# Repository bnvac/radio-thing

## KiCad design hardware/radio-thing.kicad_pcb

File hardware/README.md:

# Radio Thing — main board, rev A (KiCad 9)

One PCB for both builds:

- **POD:** 82 × 50 mm. Cut the button tab off at its 5 small bridges (flush cutters or a saw, then sand).
- **DISPLAY:** 82 × 72 mm. Keeps the tab with 3 buttons (UP · OK · DOWN) centred right under the screen.

## Status

| Step | State |
|---|---|
| Schematic | ✅ Generated, KiCad ERC: 1 warning (unused IMU aux pin tied to GND, expected) |
| Netlist | ✅ 304 pin assignments verified against `design.py`, 30 MCU pins verified against `firmware/include/board_pins.h` |
| PCB placement | ✅ Power stages and sensors placed tight around their IC pins; every pad on its net. |
| PCB routing | ✅ **Fully routed** (multi-pass Freerouting + fixed USB-C and U3 ground patterns): 932 track segments, 107 vias. DRC: **0 unconnected, 0 electrical errors, 0 schematic-parity issues**. 6 silkscreen-at-edge warnings remain, all expected (USB-C and the power switch overhang the edge by design). |
| Manufacturing files | ✅ `fab/`: Gerbers + drill (zip), and BOM + placement (CPL) for each build |
| Datasheet checks | ✅ Done 2026-10-20. 13 fixes applied; 5 items need the real parts in hand (see below). |

**Electrically complete and orderable as a prototype.** Before ordering: check the 5 open items below with real parts in hand, and look over the routing in KiCad (see "Review before ordering").

## Files

| File | What |
|---|---|
| `design.py` | **Source of truth.** Every part, value, footprint, and pin→net connection, plus the build variant. Edit this, not the KiCad files. |
| `tools/gen_schematic.py` | Generates `radio-thing.kicad_sch` + `radio-thing.kicad_sym` (custom MAX17048 symbol). Pins come from KiCad's own symbol library, so pin numbers aren't hand-typed. |
| `tools/check_netlist.py` | Checks KiCad's exported netlist against `design.py` and the firmware pin map |
| `tools/gen_pcb.py` | Generates the placed board: outline with break-off slots, 4 layers (In1 = solid GND), cluster placement around each IC, edge keep-outs, the fixed USB-C pattern, nets from the netlist |
| `route.sh` | Autoroutes the placed board (Freerouting 1.9.0, up to three passes), adds GND pours on top/bottom, fills, runs DRC |
| `tools/finish_pcb.py`, `tools/silk_cleanup.py` | Route import, pours, fill, silkscreen tidy-up, place/drill origin |
| `tools/fab_outputs.py` | Writes `fab/`: Gerber+drill zip, `bom-POD.csv`, `bom-DISPLAY.csv`, `cpl-POD.csv`, `cpl-DISPLAY.csv` (JLCPCB column format) |
| `build.sh` | Regenerates schematic + placed board, runs ERC, netlist check, DRC, BOM, PDF |
| `radio-thing.kicad_pcb` | **The routed board** (output of `route.sh`) |
| `bom.csv` | BOM grouped by value/footprint/**Variant** (BOTH / POD / DISP) |
| `radio-thing-schematic.pdf` | Printable schematic |
| `reports/` | Latest ERC/DRC reports and router logs |

Full rebuild:
```sh
export KICAD_SYMBOL_DIR=…/kicad-symbols KICAD_FOOTPRINT_DIR=…/kicad-footprints   # KiCad 9 libraries
./build.sh                                             # schematic + placed board + checks
FREEROUTING_JAR=…/freerouting-1.9.0.jar ./route.sh     # needs Java 17+ and xvfb-run
python3 tools/fab_outputs.py                           # Gerbers, drill, BOM, CPL
```

> If you hand-edit the routing in KiCad, **stop running build.sh/route.sh**, because they regenerate the board from scratch. From then on, edit in KiCad and use *Tools → Update PCB from Schematic*. `design.py` is then documentation only.

## Block diagram

```
USB-C ─ F1 ─ U1 ESD ─┬─ VBUS ─ U2 BQ24074 (power path, ~1 A in, 445 mA charge)
                     │            ├─ VBAT ─ J2 LiPo 1S ── U3 MAX17048 fuel gauge (I2C)
                     │            └─ VSYS ─┬─ SW1 power ─ U4 TPS63001 ─ +3V3 (ESP32, sensors, display)
                     │                     ├─ U5 TPS61202 ─ FB1/C13 LC filter ─ +5V_HEAD ─ J4 radar head [POD]
                     │                     └─ BZ1 buzzer [DISP]
                     └─ USB D+/D- ─ U6 ESP32-S3-WROOM-1U (U.FL → SMA)
U6 ── I2C ── U7 ISM330DHCX (IMU) + U8 LIS2MDL (compass) + U3
U6 ── SPI ── J3 ST7796 3.5" display [DISP]
U6 ── UART1/UART2 + HEAD_ID + HEAD_EN ── J4 JST-GH 10p radar head [POD]
U6 ── 3 buttons UP/OK/DOWN [DISP] (OK on both builds), RGB LED, buzzer
```

## Build variants

| Variant | Fitted on | Parts |
|---|---|---|
| BOTH | every board | USB-C, charger, fuel gauge, 3V3, ESP32, sensors, LED, OK button |
| POD | pod | 5 V boost + filter, radar head connector J4, head ID |
| DISP | display | display socket + backlight resistor, UP and DOWN buttons, buzzer. Change **R7 to 1k** for ~890 mA charging of a 2000 mAh cell. |

## Pin map (ESP32-S3-WROOM-1U-N8R8)

Defined in `firmware/include/board_pins.h`, the single source of truth, and checked automatically.

| GPIO | Net | GPIO | Net |
|---|---|---|---|
| 0 | BOOT | 15 | spare (TP2) |
| 1 | HEAD_ID (ADC) | 16 | BUZZER |
| 2 | HEADB_RX | 17 | CHG_N |
| 4 | BTN_UP | 18 | I2C_SCL |
| 5 | BTN_DOWN | 19/20 | USB D-/D+ |
| 6 | BTN_OK (wake) | 21 | LCD_BL |
| 7 | spare (TP1) | 38/47/48 | LED R/G/B |
| 8 | I2C_SDA | 39/40 | HEADA TX/RX |
| 9 | LCD_DC | 41 | HEAD_EN |
| 10 | SPI_CS | 42 | HEADB_TX |
| 11/12/13 | MOSI/SCK/MISO | 43/44 | debug UART |
| 14 | LCD_RST | 3, 45, 46, 35–37 | unused (strapping / PSRAM) |

GPIO7 and GPIO15 are spare (test pads TP1/TP2), e.g. for an IMU interrupt or touch later.

**Buttons (3, under the screen):** UP short = up/zoom in, hold = cycle mode · OK short = select/menu, hold 1.5 s = back (map: next pod), hold 3 s = sleep · DOWN short = down/zoom out. The buttons are centred on board x = 48.8 mm, which is the centre line of the enclosure. The 98 mm screen is centred in the case and connects to J3 with a short 14-wire ribbon (see `../enclosure/README.md`).

## Datasheet check (2026-10-20)

Every value that came from memory was checked against the manufacturer datasheets: TI BQ2407x SLUS810N, TPS6300x SLVS520C, TPS6120x SLVS577E, Maxim MAX17048 19-6171 r7, ST ISM330DHCX r4, LIS2MDL r5, Qorvo DWM3000 rev B, Espressif WROOM-1/1U v1.8, Hi-Link LD2450 protocol v1.03, and lcdwiki MSP3525/3526.

**Fixed after the check**

| Part | Was | Now | Why |
|---|---|---|---|
| R6 BQ24074 ITERM | 15k | **3.0k** | 15k ends the charge at 50% of ICHG (the max allowed). 3.0k gives the normal 10%. |
| R4 BQ24074 ILIM | 1.5k (~1.07 A) | **1.78k (~0.9 A)** | Stay within a default USB-C source's 900 mA |
| L1 TPS63001 | 1.5 µH | **2.2 µH** | The value TI characterises. Loop compensation assumes it. |
| TPS63001 VINA | direct | **100 Ω + 100 nF RC** | TI reference circuit |
| C11 TPS61202 VOUT | 10 µF | **22 µF** | Datasheet minimum ≈ 5 × L = 11 µF, before DC-bias derating |
| C20 LIS2MDL C1 | 100 nF | **220 nF** | Required value (Table 2). Plus **10 µF** on Vdd (C25). |
| C5 MAX17048 VDD | 1 µF | 100 nF | Datasheet value |
| Display power | +3V3 | **switched VSYS (PWR_EN)** | The module has its own 3.3 V LDO, and powering it from 3V3 would starve the backlight. Using the switched rail keeps it fully off when SW1 is off. |
| Backlight drive | P-FET high-side switch | **GPIO → 100 Ω → LED pin** | On the MSP3525 the LED pin is a logic input with a pull-up, so the old switch could never turn the backlight off |
| J3 pin 14 | NC | **SD_CS pulled high** | The module's SD card shares MISO |
| Buzzer | from VSYS (4.4 V, ~8.5 Ω coil) | **+3V3 via 15 Ω, flyback on coil** | The transducer is rated 2–4 V and ≤150 mA mean |
| Radar head UART | direct | **100 Ω series ×4** | Detachable connector: limits back-powering and ESD |
| Button tab | no holes | **2 × M3 holes** | Button presses would otherwise bend the board at the break line |
| Tab break line | V-score | **routed slots + 5 solid bridges** | A V-cut severs every copper layer, which would cut the button traces on the DISPLAY build too |
| DWM3000 option | footprint on board | **removed from rev A** | Its antenna keep-out blocked routing; pod-to-pod ranging moves to rev B |

**Confirmed correct:**
- BQ24074 pinout, EN1/EN2 mode, ISET (445 mA / 890 mA), TMR 46.4k (6.2 h), TS 10k, /CE, caps.
- TPS63001 pinout, PS/SYNC, FB, current margin.
- TPS61202 pinout, PS, UVLO-to-VIN, load disconnect, 2.2 µH, 600 mA at 5 V.
- MAX17048 pinout, wiring and registers.
- ISM330DHCX pinout, unused-pin handling and registers.
- LIS2MDL pinout, CS and address.
- ESP32-S3 strapping, EN RC, PSRAM pins, module pin numbers.
- LD2450 needs 5 V / >200 mA with a 3.3 V UART at 256000 baud.

**Still open (check with the real parts):**
1. **Display:** buy the **lcdwiki MSP3525 (ST7796)** module; the board is wired for its pinout. MSP3520/3521 is an ILI9488 board with different touch pins. The module is 98 × 55.5 mm with the header centred on its short edge, so check J3 and the button positions against the module before ordering.
2. **Buzzer:** KCG0601 has no datasheet online. Buy any 3 V, ~3 kHz, 6.5 mm external-drive magnetic transducer and confirm its footprint.
3. **MAX17048:** exposed-pad size (0.8 × 1.2 mm in the footprint) vs Maxim land pattern 90-0065. Also check stock/lifecycle.
4. **USBLC6-2SC6:** pinout confirmed from secondary sources only.
5. **LD2450 head board:** connector pin order and pitch (only shown as an image in Hi-Link's manual).

## Routing notes

- **Stackup:** F.Cu parts/signals · In1 solid GND · In2 power + signals · B.Cu signals. GND pours on F.Cu and B.Cu. Power ICs' thermal pads have solid (not spoked) GND connections.
- **Traces:** signals 0.2 mm / 0.127 mm clearance; power nets 0.3 mm (about 1.3 A on outer 1 oz copper at a 20 °C rise, above the ~1.2 A worst case on VSYS). Vias 0.6/0.3 mm (power 0.8/0.4).
- **Power stages:** each converter's inductor and input/output capacitors sit directly at the IC pins (placed by `gen_pcb.py` around U2/U4/U5), so the switching loops are short.
- **USB:** D+/D- are full-speed (12 Mbit/s), so no controlled impedance is needed. The two orientation pin pairs on the USB-C connector are joined with a fixed pattern (D- loop on top, D+ jumper on the bottom via two vias).
- **Edges:** tracks and vias stay at least 0.35 mm from every edge and slot.
- **Break-off tab:** 4 routed slots (1.5 mm wide) with 5 bridges (three 6–7 mm bridges in the middle carry the button traces). The button traces cross through the bridges, so the DISPLAY build keeps them intact. For the POD build, cut the bridges.

## Review before ordering

The routing came from an autorouter, so give it a look in KiCad before you pay for boards:
1. Open `radio-thing.kicad_pcb` and run DRC (it should show only the 6 expected silkscreen-edge warnings).
2. Look at the power stages (U2, U4, U5): short, direct connections from the inductors and caps to the IC pins.
3. Check the 5 open part items above. The display module position matters most.
4. **Fab:** JLCPCB 4-layer, 1.6 mm, 1 oz, ENIG. Upload `fab/radio-thing-revA-gerbers.zip`. For assembly, upload the BOM + CPL for the build you want (`bom-POD.csv` + `cpl-POD.csv`, or the DISPLAY pair). Fill in the LCSC part numbers, and check part rotations in their preview. The 12 mm buttons, display socket and debug header are through-hole: hand-solder them or select THT assembly.
5. **Mechanical:** M3 holes at the corners and on the tab, an SMA bulkhead pigtail from the U6 U.FL, and display standoffs.

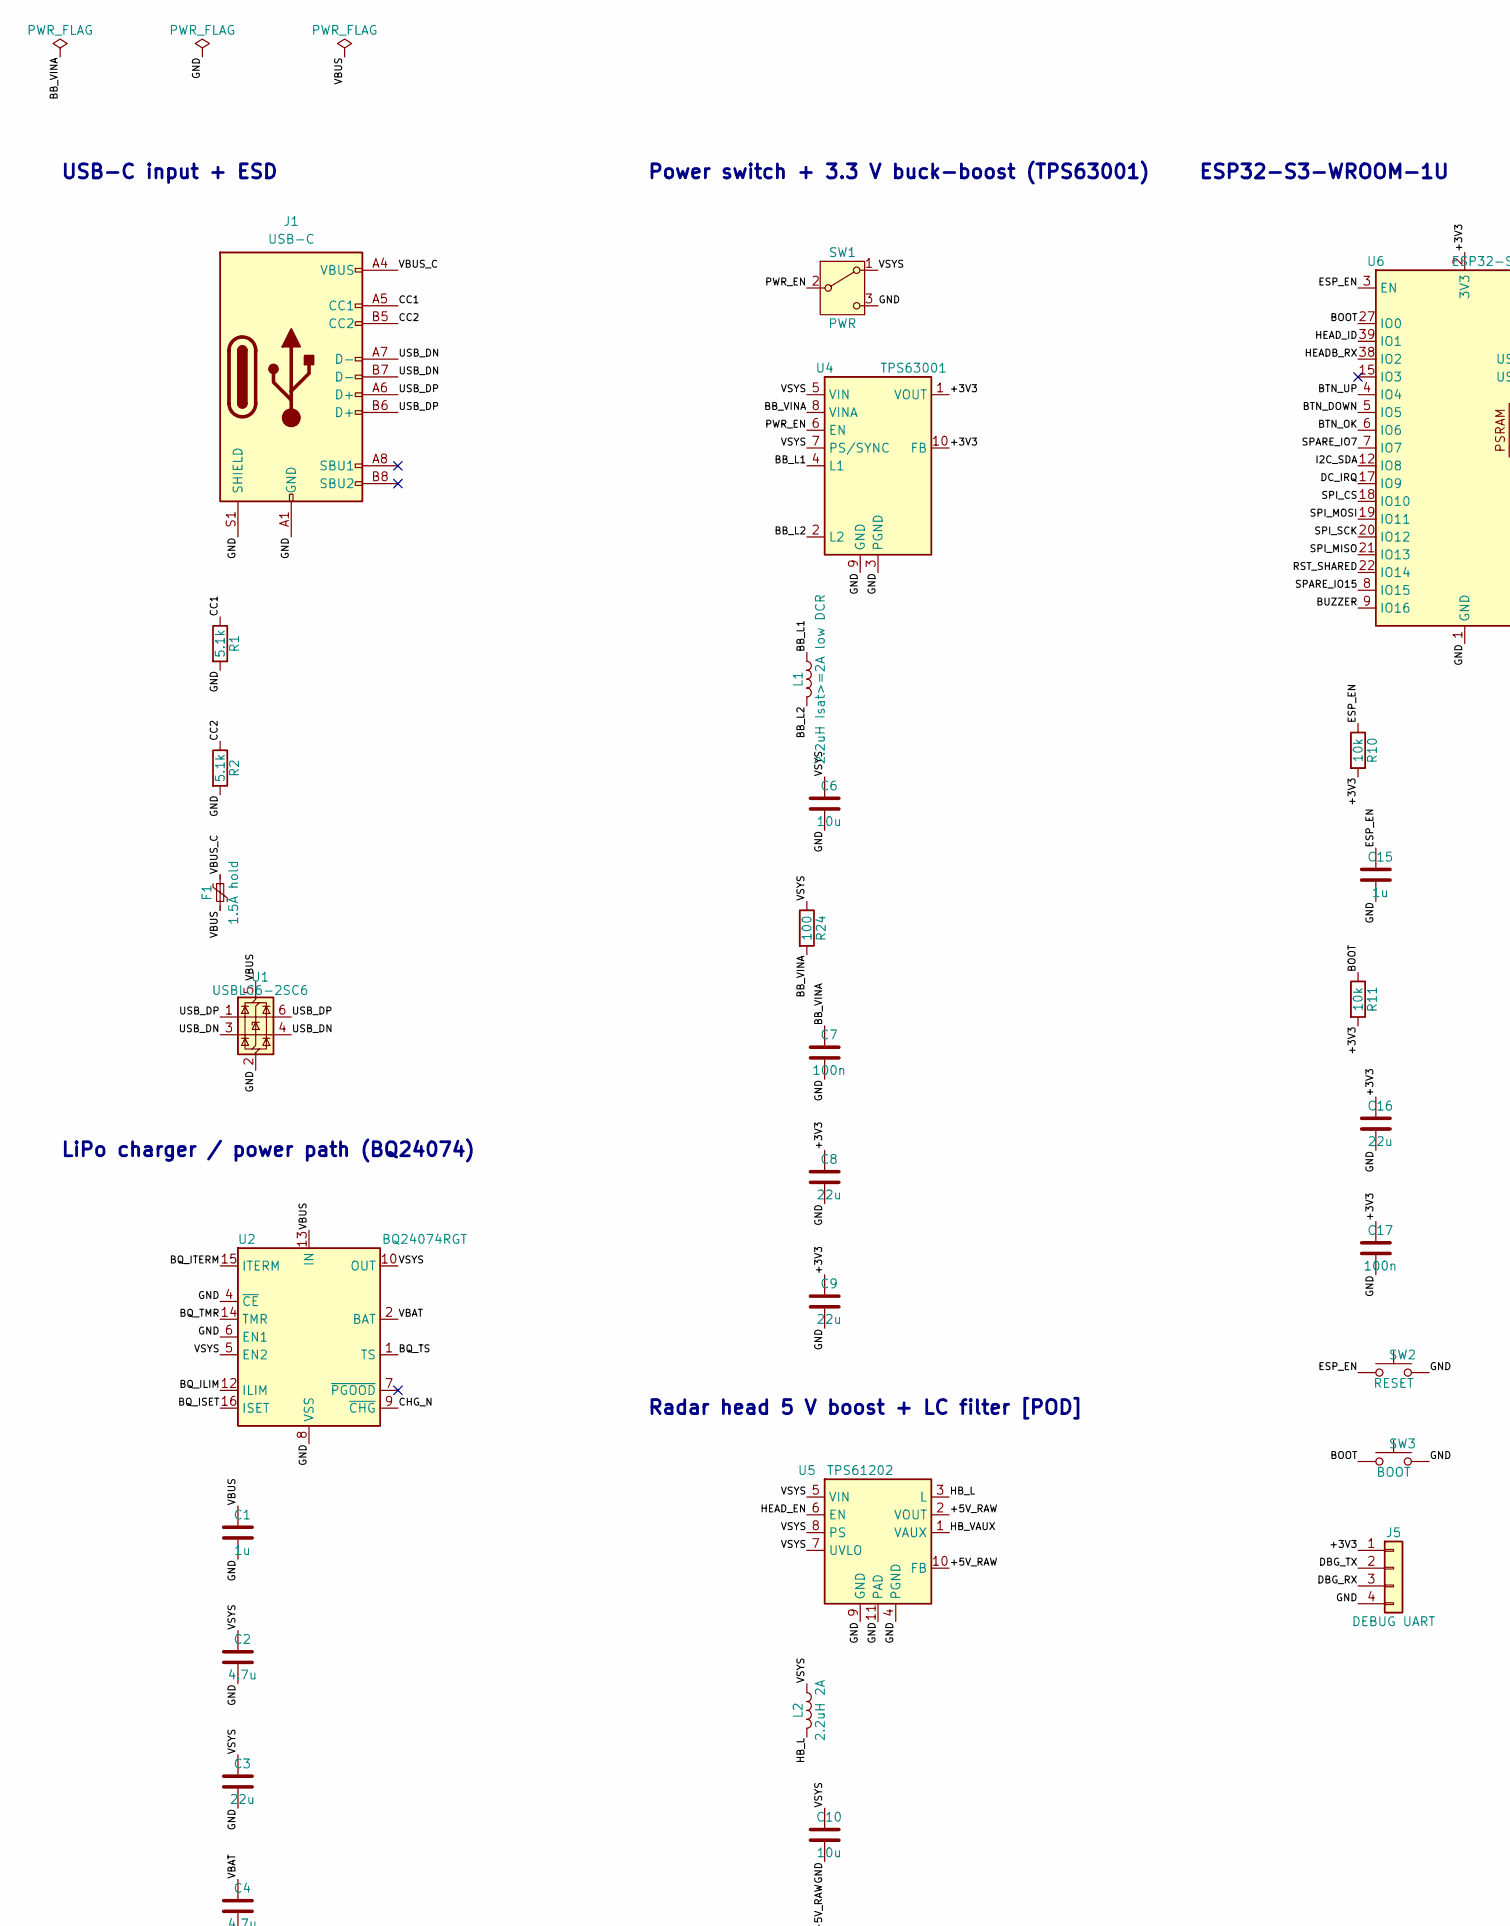
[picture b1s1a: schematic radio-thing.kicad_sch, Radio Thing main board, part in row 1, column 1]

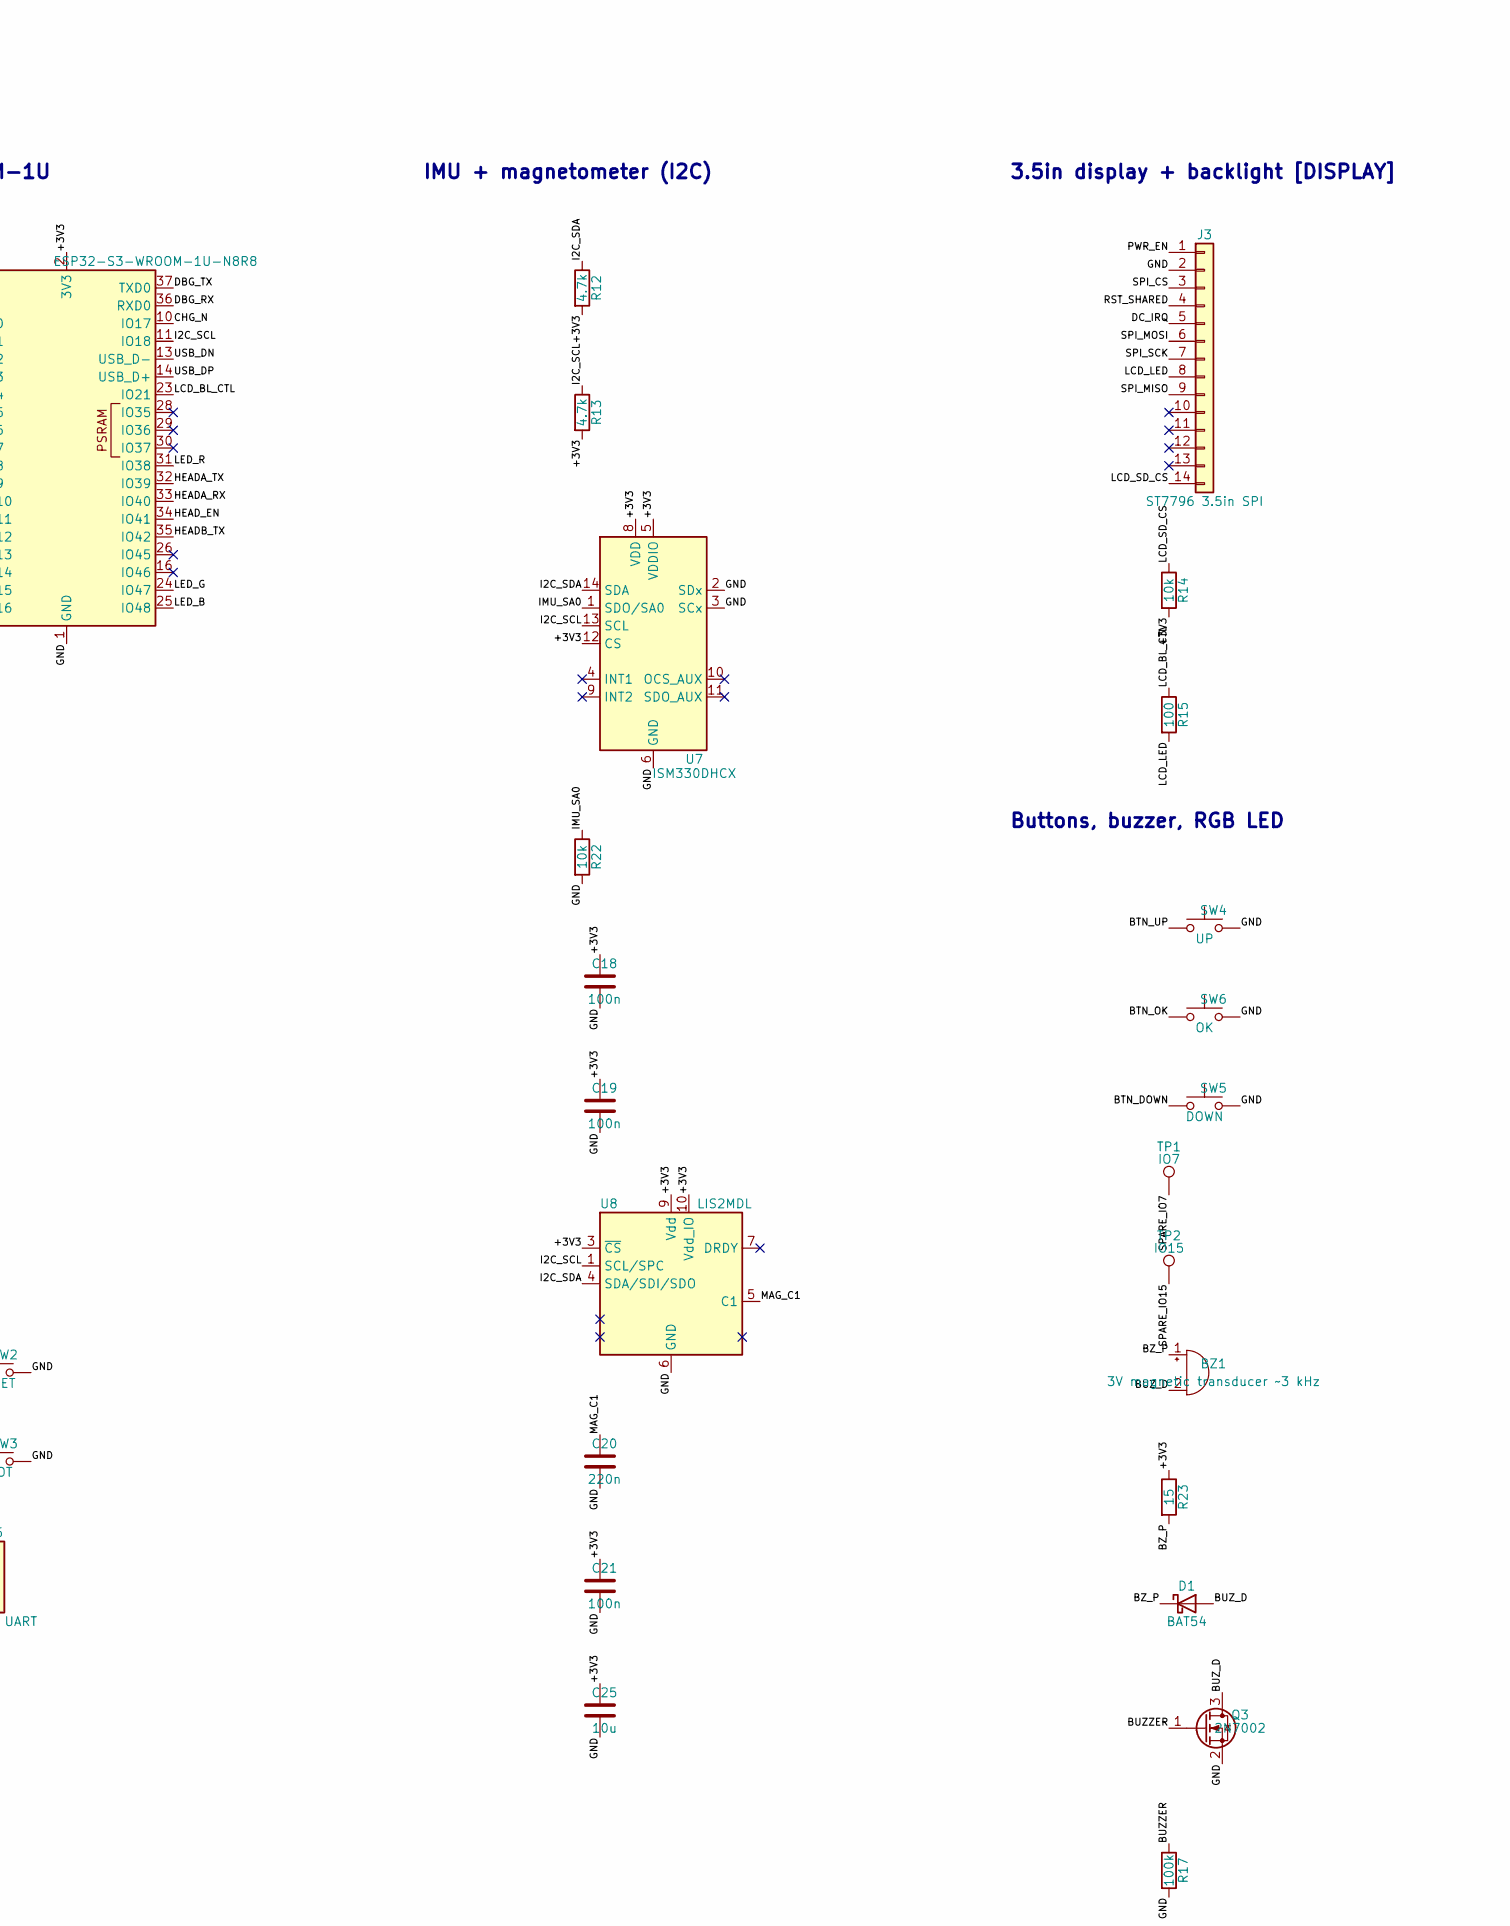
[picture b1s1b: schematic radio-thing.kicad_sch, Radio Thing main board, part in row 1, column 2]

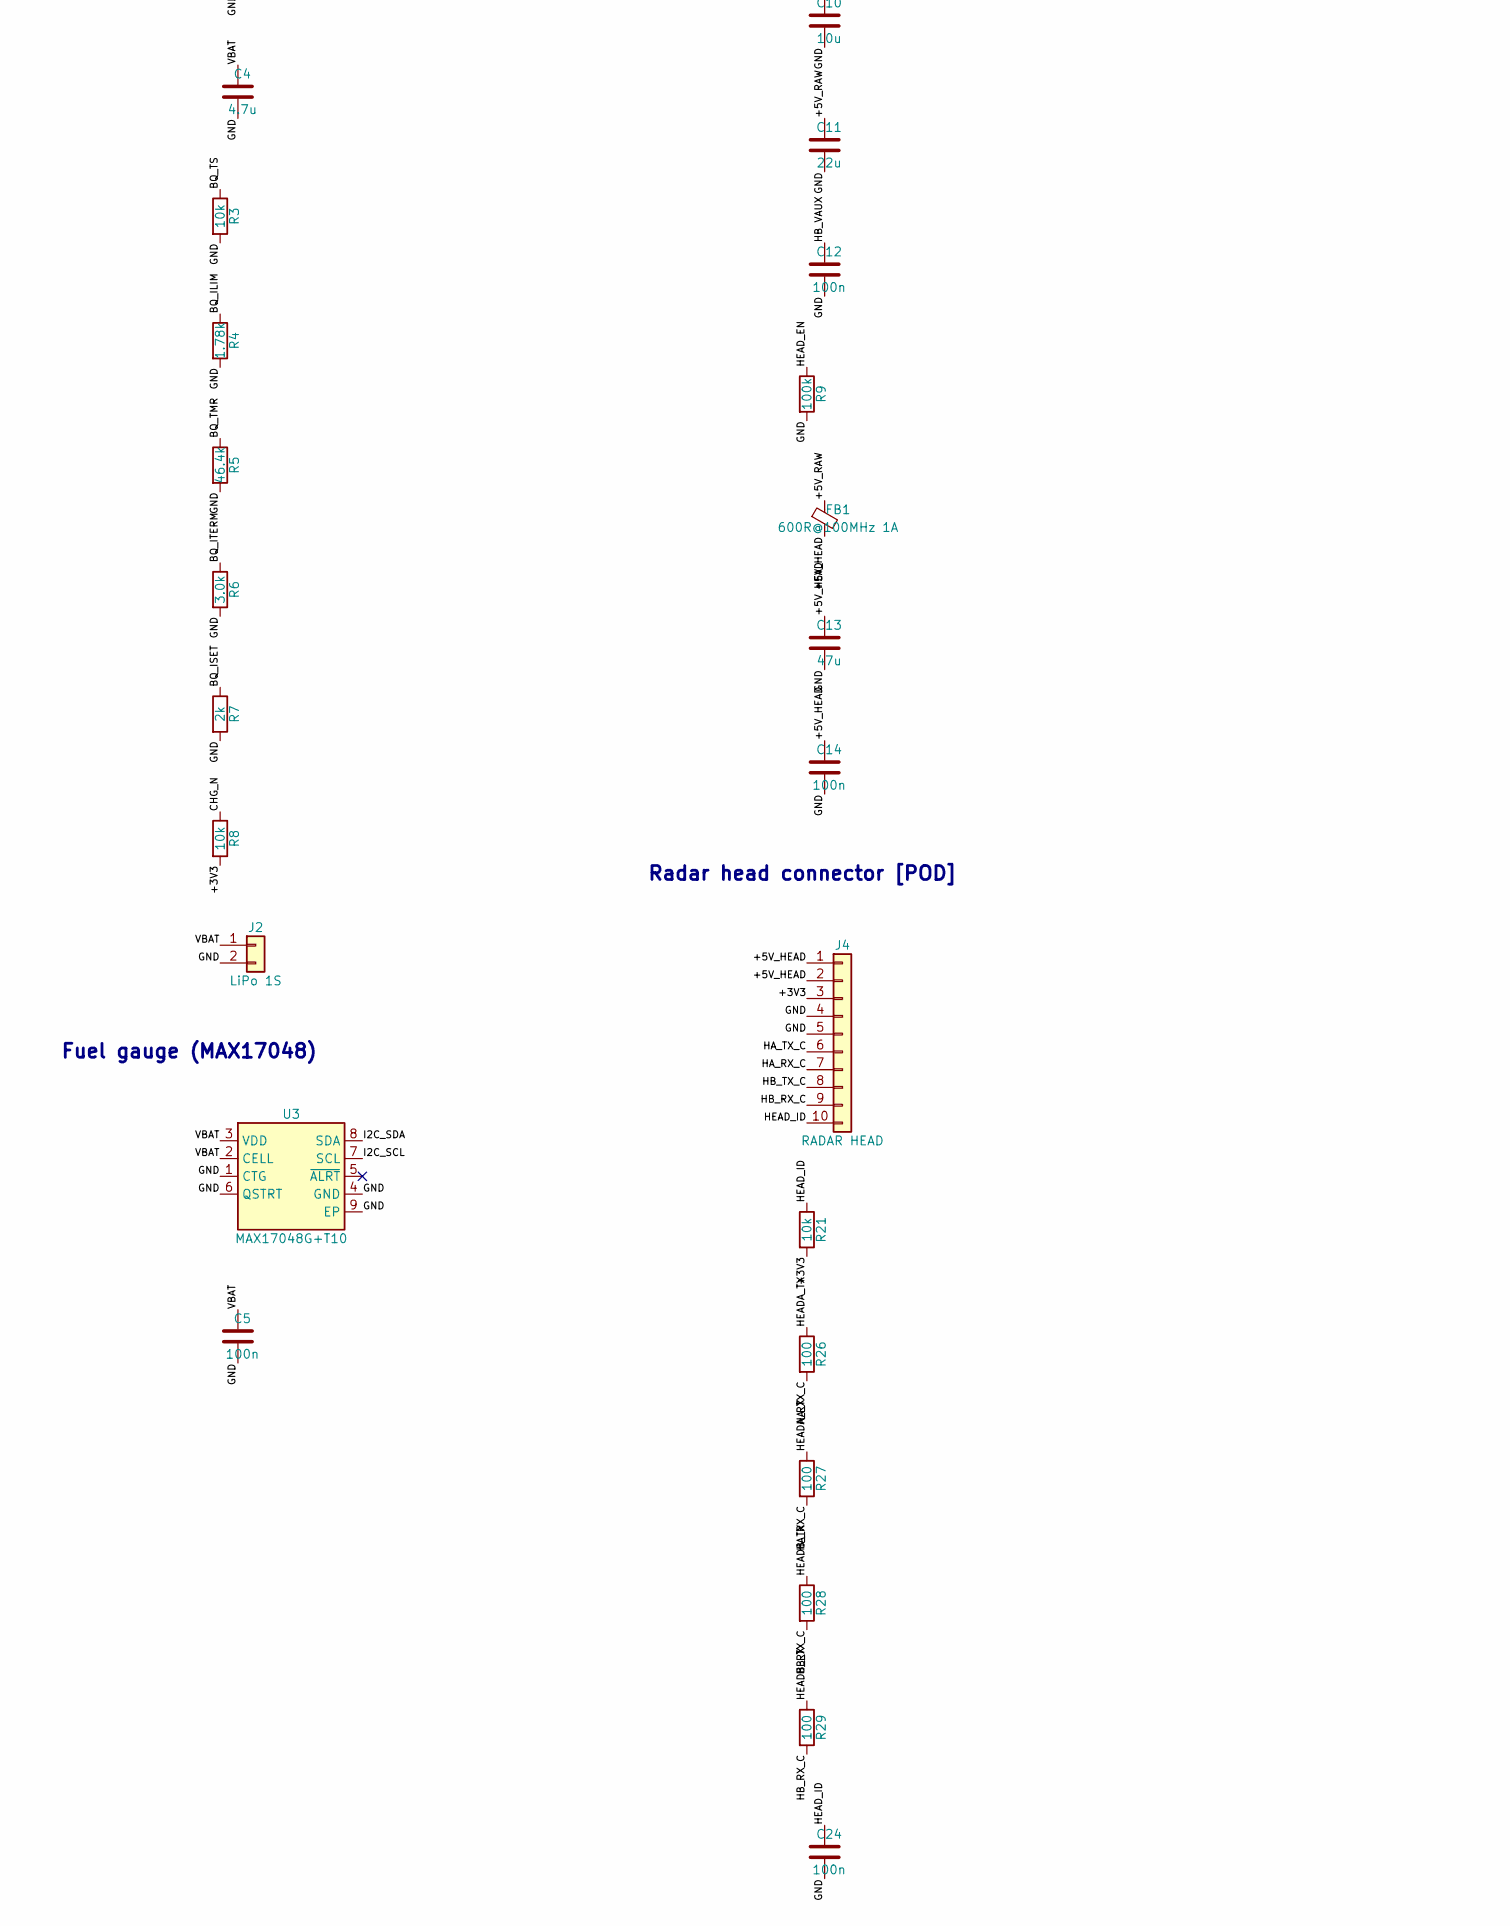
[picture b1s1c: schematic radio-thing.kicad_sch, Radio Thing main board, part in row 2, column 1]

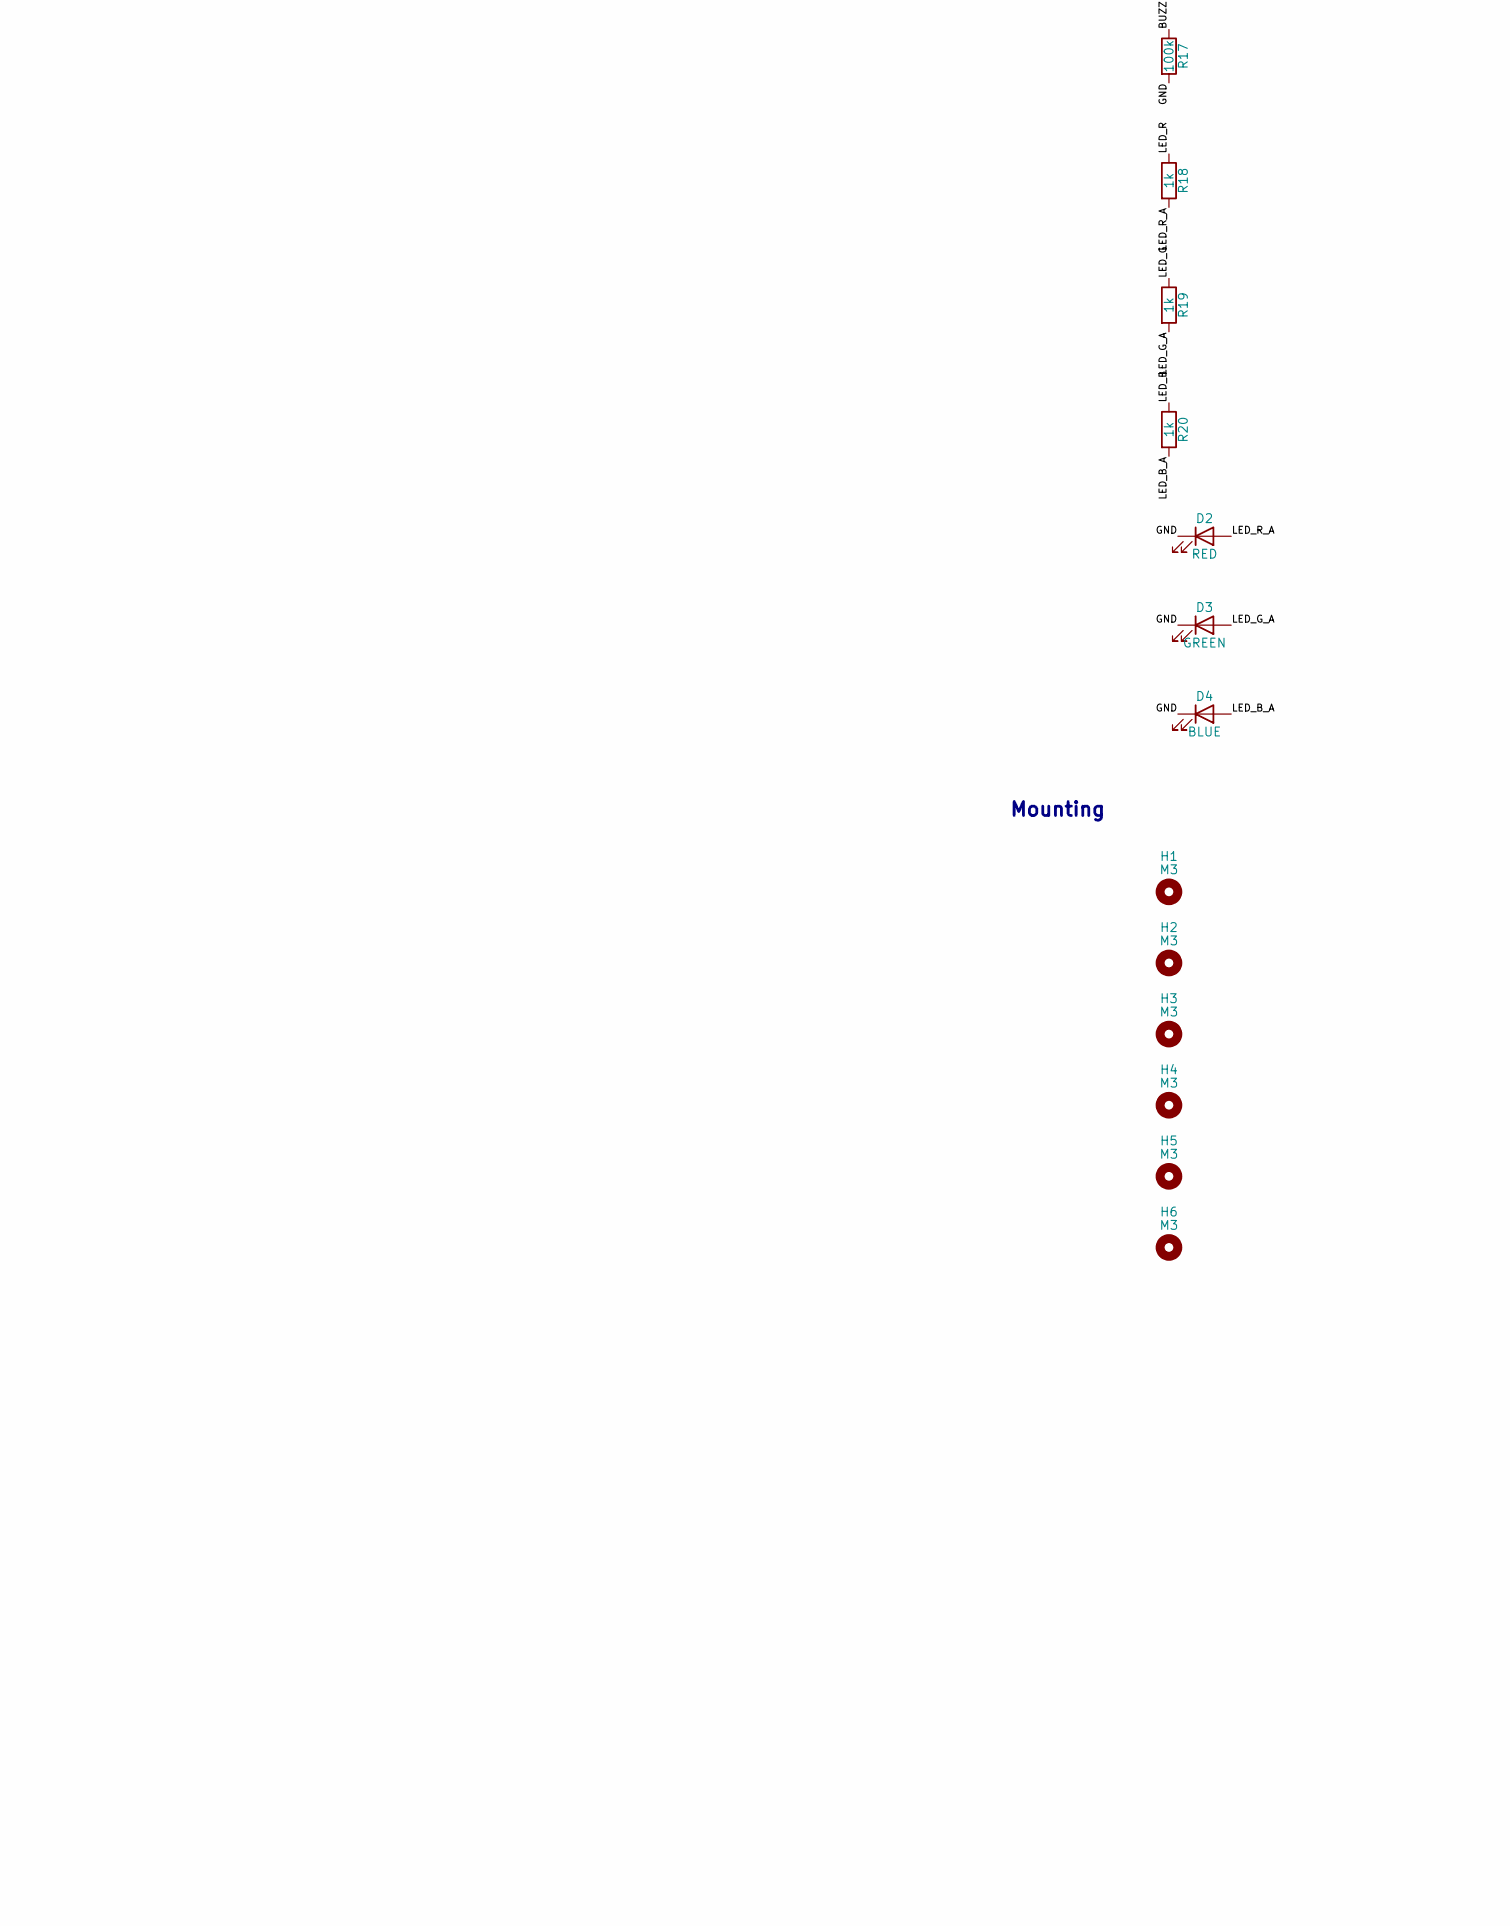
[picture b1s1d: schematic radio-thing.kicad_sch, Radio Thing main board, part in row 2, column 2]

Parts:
BZ1: 3V magnetic transducer ~3 kHz; MagneticBuzzer_Kingstate_KCG0601
C1: 1u; C_0603_1608Metric
C2, C4: 4.7u; C_0603_1608Metric
C3, C8, C9, C11, C16: 22u; C_0805_2012Metric
C5, C7, C12, C14, C17, C18, C19, C21, C24: 100n; C_0402_1005Metric
C6, C10: 10u; C_0805_2012Metric
C13: 47u; C_1206_3216Metric
C15: 1u; C_0402_1005Metric
C20: 220n; C_0402_1005Metric
C25: 10u; C_0603_1608Metric
D1: BAT54; D_SOD-123
D2: RED; LED_0603_1608Metric
D3: GREEN; LED_0603_1608Metric
D4: BLUE; LED_0603_1608Metric
F1: 1.5A hold; Fuse_1206_3216Metric
FB1: 600R@100MHz 1A; L_0805_2012Metric
H1, H2, H3, H4, H5, H6: M3; MountingHole_3.2mm_M3
J1: USB-C; USB_C_Receptacle_HRO_TYPE-C-31-M-12
J2: LiPo 1S; JST_PH_S2B-PH-SM4-TB_1x02-1MP_P2.00mm_Horizontal
J3: ST7796 3.5in SPI; PinSocket_1x14_P2.54mm_Vertical
J4: RADAR HEAD; JST_GH_SM10B-GHS-TB_1x10-1MP_P1.25mm_Horizontal
J5: DEBUG UART; PinHeader_1x04_P2.54mm_Vertical
L1: 2.2uH Isat>=2A low DCR; L_Taiyo-Yuden_NR-40xx
L2: 2.2uH 2A; L_Taiyo-Yuden_NR-40xx
Q3: 2N7002; SOT-23
R1, R2: 5.1k; R_0402_1005Metric
R3, R8, R10, R11, R14, R21, R22: 10k; R_0402_1005Metric
R4: 1.78k; R_0402_1005Metric
R5: 46.4k; R_0402_1005Metric
R6: 3.0k; R_0402_1005Metric
R7: 2k; R_0402_1005Metric
R9, R17: 100k; R_0402_1005Metric
R12, R13: 4.7k; R_0402_1005Metric
R15, R24, R26, R27, R28, R29: 100; R_0402_1005Metric
R18, R19, R20: 1k; R_0402_1005Metric
R23: 15; R_0402_1005Metric
SW1: PWR; SW_SPDT_PCM12
SW2: RESET; SW_Push_SPST_NO_Alps_SKRK
SW3: BOOT; SW_Push_SPST_NO_Alps_SKRK
SW4: UP; SW_PUSH-12mm
SW5: DOWN; SW_PUSH-12mm
SW6: OK; SW_PUSH-12mm
TP1: IO7; TestPoint_Pad_D1.5mm
TP2: IO15; TestPoint_Pad_D1.5mm
U1: USBLC6-2SC6; SOT-23-6
U2: BQ24074RGT; VQFN-16-1EP_3x3mm_P0.5mm_EP1.6x1.6mm
U3: MAX17048G+T10; TDFN-8-1EP_2x2mm_P0.5mm_EP0.8x1.2mm
U4: TPS63001; Texas_DRC0010J_ThermalVias
U5: TPS61202; Texas_S-PVSON-N10_ThermalVias
U6: ESP32-S3-WROOM-1U-N8R8; ESP32-S3-WROOM-1U
U7: ISM330DHCX; LGA-14_3x2.5mm_P0.5mm_LayoutBorder3x4y
U8: LIS2MDL; LGA-12_2x2mm_P0.5mm

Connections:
/+3V3: C8.1, C9.1, C16.1, C17.1, C18.1, C19.1, C21.1, C25.1, J4.3, J5.1, R8.2, R10.2, R11.2, R12.2, R13.2, R14.2, R21.2, R23.1, U4.1 (VOUT), U4.10 (FB), U6.2 (3V3), U7.5 (VDDIO), U7.8 (VDD), U7.12 (CS), U8.3 (~CS), U8.9 (Vdd), U8.10 (Vdd_IO)
/+5V_HEAD: C13.1, C14.1, FB1.2, J4.1, J4.2
/+5V_RAW: C11.1, FB1.1, U5.2 (VOUT), U5.10 (FB)
/BB_L1: L1.1, U4.4 (L1)
/BB_L2: L1.2, U4.2 (L2)
/BB_VINA: C7.1, R24.2, U4.8 (VINA)
/BOOT: R11.1, SW3.1, U6.27 (IO0)
/BQ_ILIM: R4.1, U2.12 (ILIM)
/BQ_ISET: R7.1, U2.16 (ISET)
/BQ_ITERM: R6.1, U2.15 (ITERM)
/BQ_TMR: R5.1, U2.14 (TMR)
/BQ_TS: R3.1, U2.1 (TS)
/BTN_DOWN: SW5.1, U6.5 (IO5)
/BTN_OK: SW6.1, U6.6 (IO6)
/BTN_UP: SW4.1, U6.4 (IO4)
/BUZZER: Q3.1 (G), R17.1, U6.9 (IO16)
/BUZ_D: BZ1.2 (-), D1.2 (A), Q3.3 (D)
/BZ_P: BZ1.1 (+), D1.1 (K), R23.2
/CC1: J1.A5 (CC1), R1.1
/CC2: J1.B5 (CC2), R2.1
/CHG_N: R8.1, U2.9 (~CHG), U6.10 (IO17)
/DBG_RX: J5.3, U6.36 (RXD0)
/DBG_TX: J5.2, U6.37 (TXD0)
/DC_IRQ: J3.5, U6.17 (IO9)
/ESP_EN: C15.1, R10.1, SW2.1, U6.3 (EN)
/GND: C1.2, C2.2, C3.2, C4.2, C5.2, C6.2, C7.2, C8.2, C9.2, C10.2, C11.2, C12.2, C13.2, C14.2, C15.2, C16.2, C17.2, C18.2, C19.2, C20.2, C21.2, C24.2, C25.2, D2.1 (K), D3.1 (K), D4.1 (K), J1.A1 (GND), J1.A12 (GND), J1.B1 (GND), J1.B12 (GND), J1.S1 (SHIELD), J2.2, J3.2, J4.4, J4.5, J5.4, Q3.2 (S), R1.2, R2.2, R3.2, R4.2, R5.2, R6.2, R7.2, R9.2, R17.2, R22.2, SW1.3 (C), SW2.2, SW3.2, SW4.2, SW5.2, SW6.2, U1.2 (GND), U2.4 (~CE), U2.6 (EN1), U2.8 (VSS), U2.17 (VSS), U3.1 (CTG), U3.4 (GND), U3.6 (QSTRT), U3.9 (EP), U4.3 (PGND), U4.9 (GND), U4.11 (PGND), U5.4 (PGND), U5.9 (GND), U5.11 (PAD), U6.1 (GND), U6.40 (GND), U6.41 (GND), U7.2 (SDx), U7.3 (SCx), U7.6 (GND), U7.7 (GND), U8.6 (GND), U8.8 (GND)
/HA_RX_C: J4.7, R27.2
/HA_TX_C: J4.6, R26.2
/HB_L: L2.2, U5.3 (L)
/HB_RX_C: J4.9, R29.2
/HB_TX_C: J4.8, R28.2
/HB_VAUX: C12.1, U5.1 (VAUX)
/HEADA_RX: R27.1, U6.33 (IO40)
/HEADA_TX: R26.1, U6.32 (IO39)
/HEADB_RX: R29.1, U6.38 (IO2)
/HEADB_TX: R28.1, U6.35 (IO42)
/HEAD_EN: R9.1, U5.6 (EN), U6.34 (IO41)
/HEAD_ID: C24.1, J4.10, R21.1, U6.39 (IO1)
/I2C_SCL: R13.1, U3.7 (SCL), U6.11 (IO18), U7.13 (SCL), U8.1 (SCL/SPC)
/I2C_SDA: R12.1, U3.8 (SDA), U6.12 (IO8), U7.14 (SDA), U8.4 (SDA/SDI/SDO)
/IMU_SA0: R22.1, U7.1 (SDO/SA0)
/LCD_BL_CTL: R15.1, U6.23 (IO21)
/LCD_LED: J3.8, R15.2
/LCD_SD_CS: J3.14, R14.1
/LED_B: R20.1, U6.25 (IO48)
/LED_B_A: D4.2 (A), R20.2
/LED_G: R19.1, U6.24 (IO47)
/LED_G_A: D3.2 (A), R19.2
/LED_R: R18.1, U6.31 (IO38)
/LED_R_A: D2.2 (A), R18.2
/MAG_C1: C20.1, U8.5 (C1)
/PWR_EN: J3.1, SW1.2 (B), U4.6 (EN)
/RST_SHARED: J3.4, U6.22 (IO14)
/SPARE_IO7: TP1.1, U6.7 (IO7)
/SPARE_IO15: TP2.1, U6.8 (IO15)
/SPI_CS: J3.3, U6.18 (IO10)
/SPI_MISO: J3.9, U6.21 (IO13)
/SPI_MOSI: J3.6, U6.19 (IO11)
/SPI_SCK: J3.7, U6.20 (IO12)
/USB_DN: J1.A7 (D-), J1.B7 (D-), U1.3 (I/O2), U1.4 (I/O2), U6.13 (USB_D-)
/USB_DP: J1.A6 (D+), J1.B6 (D+), U1.1 (I/O1), U1.6 (I/O1), U6.14 (USB_D+)
/VBAT: C4.1, C5.1, J2.1, U2.2 (BAT), U2.3 (BAT), U3.2 (CELL), U3.3 (VDD)
/VBUS: C1.1, F1.2, U1.5 (VBUS), U2.13 (IN)
/VBUS_C: F1.1, J1.A4 (VBUS), J1.A9 (VBUS), J1.B4 (VBUS), J1.B9 (VBUS)
/VSYS: C2.1, C3.1, C6.1, C10.1, L2.1, R24.1, SW1.1 (A), U2.5 (EN2), U2.10 (OUT), U2.11 (OUT), U4.5 (VIN), U4.7 (PS/SYNC), U5.5 (VIN), U5.7 (UVLO), U5.8 (PS)

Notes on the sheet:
USB-C input + ESD
LiPo charger / power path (BQ24074)
Fuel gauge (MAX17048)
Power switch + 3.3 V buck-boost (TPS63001)
Radar head 5 V boost + LC filter [POD]
Radar head connector [POD]
ESP32-S3-WROOM-1U
IMU + magnetometer (I2C)
3.5in display + backlight [DISPLAY]
Buttons, buzzer, RGB LED
Mounting

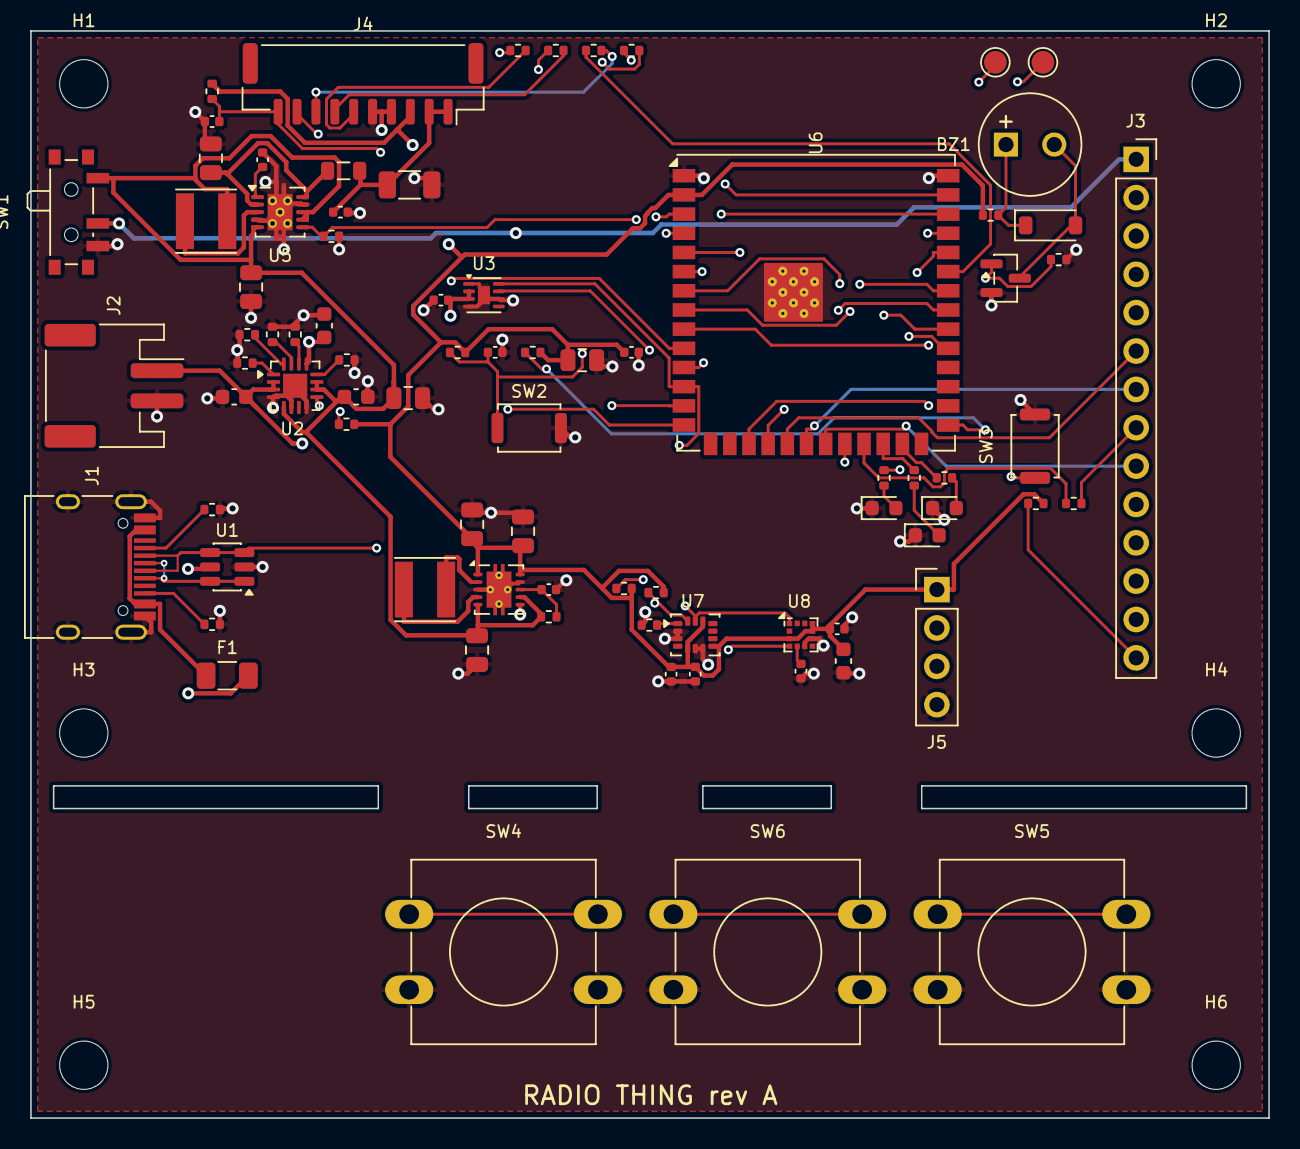
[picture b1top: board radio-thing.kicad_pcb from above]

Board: 4 copper layers, 82.0 x 72.0 mm, 87 parts (0 on the bottom side), 65 nets.

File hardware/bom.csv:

"Refs","Value","Footprint","Variant","Note","Qty","DNP"
"BZ1","3V magnetic transducer ~3 kHz","Buzzer_Beeper:MagneticBuzzer_Kingstate_KCG0601","DISP","external-drive coil (~8.5 ohm), 2-4 V, <=150 mA mean: drive with ~2.7-3 kHz square wave","1",""
"C1","1u","Capacitor_SMD:C_0603_1608Metric","BOTH","","1",""
"C2,C4","4.7u","Capacitor_SMD:C_0603_1608Metric","BOTH","","2",""
"C3,C8,C9,C16","22u","Capacitor_SMD:C_0805_2012Metric","BOTH","","4",""
"C5,C7,C17,C18,C19,C21","100n","Capacitor_SMD:C_0402_1005Metric","BOTH","MAX17048 VDD bypass 0.1 uF per datasheet,VINA filter cap","6",""
"C6","10u","Capacitor_SMD:C_0805_2012Metric","BOTH","","1",""
"C10","10u","Capacitor_SMD:C_0805_2012Metric","POD","","1",""
"C11","22u","Capacitor_SMD:C_0805_2012Metric","POD","DS min ~5*L uF = 11 uF before DC-bias derating","1",""
"C12,C14,C24","100n","Capacitor_SMD:C_0402_1005Metric","POD","","3",""
"C13","47u","Capacitor_SMD:C_1206_3216Metric","POD","","1",""
"C15","1u","Capacitor_SMD:C_0402_1005Metric","BOTH","EN RC delay","1",""
"C20","220n","Capacitor_SMD:C_0402_1005Metric","BOTH","LIS2MDL C1 = 220 nF, low ESR, right at pins 5/6 (DS Table 2)","1",""
"C25","10u","Capacitor_SMD:C_0603_1608Metric","BOTH","LIS2MDL recommends 100 nF + 10 uF on Vdd","1",""
"D1","BAT54","Diode_SMD:D_SOD-123","DISP","flyback across the coil","1",""
"D2","RED","LED_SMD:LED_0603_1608Metric","BOTH","","1",""
"D3","GREEN","LED_SMD:LED_0603_1608Metric","BOTH","","1",""
"D4","BLUE","LED_SMD:LED_0603_1608Metric","BOTH","","1",""
"F1","1.5A hold","Fuse:Fuse_1206_3216Metric","BOTH","","1",""
"FB1","600R@100MHz 1A","Inductor_SMD:L_0805_2012Metric","POD","LC filter: keep boost ripple out of the radar","1",""
"J1","USB-C","Connector_USB:USB_C_Receptacle_HRO_TYPE-C-31-M-12","BOTH","","1",""
"J2","LiPo 1S","Connector_JST:JST_PH_S2B-PH-SM4-TB_1x02-1MP_P2.00mm_Horizontal","BOTH","CHECK battery lead polarity - vendors differ","1",""
"J3","ST7796 3.5in SPI","Connector_PinSocket_2.54mm:PinSocket_1x14_P2.54mm_Vertical","DISP","lcdwiki MSP3525/MSP3526 (ST7796) pinout. VCC feeds the module's own 3.3 V LDO, so it takes switched VSYS (PWR_EN, after SW1) - fully off when switched off. Pins 10-13 = CTP (unused)","1",""
"J4","RADAR HEAD","Connector_JST:JST_GH_SM10B-GHS-TB_1x10-1MP_P1.25mm_Horizontal","POD","Latching JST-GH; head ID resistor on head board to GND","1",""
"J5","DEBUG UART","Connector_PinHeader_2.54mm:PinHeader_1x04_P2.54mm_Vertical","BOTH","","1",""
"L1","2.2uH Isat>=2A low DCR","Inductor_SMD:L_Taiyo-Yuden_NR-40xx","BOTH","TPS6300x DS Table 1 uses 2.2 uH (VLF4012-2R2)","1",""
"L2","2.2uH 2A","Inductor_SMD:L_Taiyo-Yuden_NR-40xx","POD","","1",""
"Q3","2N7002","Package_TO_SOT_SMD:SOT-23","DISP","","1",""
"R1,R2","5.1k","Resistor_SMD:R_0402_1005Metric","BOTH","USB-C sink pull-down","2",""
"R3,R8,R10,R11,R22","10k","Resistor_SMD:R_0402_1005Metric","BOTH","/CHG open-drain pull-up,SA0 low -> I2C addr 0x6A,no NTC: fixed 10k = normal temp. Fit 10k NTC in cell instead if pack has one","5",""
"R4","1.78k","Resistor_SMD:R_0402_1005Metric","BOTH","ILIM = 1610/R ~= 0.9 A input limit (USB-C default 900 mA). BQ2407x DS SLUS810N eq.1","1",""
"R5","46.4k","Resistor_SMD:R_0402_1005Metric","BOTH","fast-charge timer ~6.2 h, pre-charge ~37 min (DS 9.3.5.6)","1",""
"R6","3.0k","Resistor_SMD:R_0402_1005Metric","BOTH","termination = 10% of ICHG for any RISET (0.03*R_ITERM/R_ISET); 15k would stop at 50%","1",""
"R7","2k","Resistor_SMD:R_0402_1005Metric","BOTH","ISET = 890/R ~= 445 mA (POD 500 mAh). DISPLAY build: 1k -> ~890 mA for 2000 mAh","1",""
"R9","100k","Resistor_SMD:R_0402_1005Metric","POD","head rail off until firmware enables it","1",""
"R12,R13","4.7k","Resistor_SMD:R_0402_1005Metric","BOTH","","2",""
"R14","10k","Resistor_SMD:R_0402_1005Metric","DISP","keep the module's SD card deselected (it shares MISO)","1",""
"R15","100","Resistor_SMD:R_0402_1005Metric","DISP","LED pin is a logic input (onboard BSS138 + 10k pull-up): high/open = backlight on, low = off; PWM ok","1",""
"R17","100k","Resistor_SMD:R_0402_1005Metric","DISP","","1",""
"R18,R19,R20","1k","Resistor_SMD:R_0402_1005Metric","BOTH","","3",""
"R21","10k","Resistor_SMD:R_0402_1005Metric","POD","","1",""
"R23","15","Resistor_SMD:R_0402_1005Metric","DISP","limits coil current to ~140 mA peak / ~70 mA mean at 50% duty","1",""
"R24","100","Resistor_SMD:R_0402_1005Metric","BOTH","VINA RC filter per TPS6300x reference design","1",""
"R26,R27,R28,R29","100","Resistor_SMD:R_0402_1005Metric","POD","series R: limits back-powering/ESD on the detachable head","4",""
"SW1","PWR","Button_Switch_SMD:SW_SPDT_PCM12","BOTH","off = 3V3 rail off; battery still charges","1",""
"SW2","RESET","Button_Switch_SMD:SW_Push_SPST_NO_Alps_SKRK","BOTH","","1",""
"SW3","BOOT","Button_Switch_SMD:SW_Push_SPST_NO_Alps_SKRK","BOTH","","1",""
"SW4","UP","Button_Switch_THT:SW_PUSH-12mm","DISP","short = up/zoom in, hold = cycle mode","1",""
"SW5","DOWN","Button_Switch_THT:SW_PUSH-12mm","DISP","short = down/zoom out","1",""
"SW6","OK","Button_Switch_THT:SW_PUSH-12mm","BOTH","Fitted on both builds; pod's only button; deep-sleep wake. Hold 1.5 s = back, 3 s = sleep","1",""
"U1","USBLC6-2SC6","Package_TO_SOT_SMD:SOT-23-6","BOTH","","1",""
"U2","BQ24074RGT","Package_DFN_QFN:VQFN-16-1EP_3x3mm_P0.5mm_EP1.6x1.6mm","BOTH","EN2=1, EN1=0 -> input current limit set by R_ILIM; /CE=0 charge enabled","1",""
"U3","MAX17048G+T10","Package_DFN_QFN:TDFN-8-1EP_2x2mm_P0.5mm_EP0.8x1.2mm","BOTH","CTG and QSTRT tied to GND per datasheet; ALRT unused (polled)","1",""
"U4","TPS63001","Package_SON:Texas_DRC0010J_ThermalVias","BOTH","PS/SYNC high = forced PWM (lower, predictable ripple for the radar)","1",""
"U5","TPS61202","Package_SON:Texas_S-PVSON-N10_ThermalVias","POD","fixed 5 V; UVLO tied to VIN (unused); PS high (verify PS polarity in datasheet)","1",""
"U6","ESP32-S3-WROOM-1U-N8R8","RF_Module:ESP32-S3-WROOM-1U","BOTH","-1U variant: U.FL antenna connector -> SMA bulkhead pigtail. IO35-37 used by octal PSRAM","1",""
"U7","ISM330DHCX","Package_LGA:LGA-14_3x2.5mm_P0.5mm_LayoutBorder3x4y","BOTH","I2C addr 0x6A (SA0=0). Aux SDx/SCx tied to GND when unused (verify)","1",""
"U8","LIS2MDL","Package_LGA:LGA-12_2x2mm_P0.5mm","BOTH","I2C addr 0x1E","1",""
